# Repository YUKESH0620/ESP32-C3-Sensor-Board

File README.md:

# ESP32-C3 Smart Sensor Board

This repository contains the complete **hardware design** of a custom **ESP32-C3 based Smart Sensor Board**, including schematics, PCB layout, and documentation.

The design integrates **robust power management, multiple sensors, data storage, USB connectivity, and auto-programming**, making it suitable for **IoT, data logging, and embedded systems development**.

---

##  Board Images

###  Complete Schematic

###  PCB Layout

###  3D Views

---

##  System Architecture

### Functional Block Diagram
```text
USB-C / Li-Po Battery
│
MCP73831 Charger
│
+5V Rail
│
LM1117-3.3 LDO
│
+3.3V Rail
│
ESP32-C3 MCU
│ │ │ │
│ │ │ Microphone + MAX4466
│ │ BME280 (I2C)
│ LDR (ADC)
SD Card (SPI)
|
SPI Flash
```
---

##  Key Features

###  Power & Charging
- USB Type-C connector
- Li-Po charging using **MCP73831**
- JST battery connector
- LM1117-3.3 LDO regulator
- Power status LED

###  Microcontroller
- **ESP32-C3-WROOM-02**
- RISC-V core
- Wi-Fi + BLE
- USB-UART programmable

###  Sensors
- **BME280** – Temperature, humidity, pressure
- **Electret microphone + MAX4466 amplifier**
- **LDR photo sensor**

###  Storage
- SPI Flash memory (W25Q32)
- Micro SD card module (SPI)

###  Programming & Debug
- CP2102N USB-to-UART
- Auto-programming (DTR/RTS → EN/BOOT)
- Boot & Reset buttons
- Test points

---

##  Working Principle

### Power Section
- USB-C provides 5V
- MCP73831 safely charges Li-Po battery
- LM1117 converts 5V to regulated 3.3V
- Decoupling capacitors ensure stable rails

### MCU & Sensors
- ESP32-C3 communicates with:
  - BME280 via I²C
  - SD card & Flash via SPI
  - Microphone and LDR via ADC
- Data can be logged or transmitted wirelessly

### Programming
- USB-C → CP2102N
- DTR/RTS control BOOT & EN automatically
- Compatible with ESP-IDF and Arduino

---

## 🧾 Bill of Materials

###  Active Components

| Ref | Component | Value / Part |
|----|----------|-------------|
| U1 | ESP32 MCU | ESP32-C3-WROOM-02 |
| U2 | Env Sensor | BME280 |
| U3 | USB-UART | CP2102N |
| U4 | Charger IC | MCP73831 |
| U5 | LDO Regulator | LM1117-3.3 |
| U6 | SPI Flash | W25Q32 |
| U7 | Mic Amplifier | MAX4466 |
| J1 | USB Connector | USB Type-C |
| J2 | Battery Connector | JST-PH-2 |
| J3 | SD Card Socket | SPI SD |

---

###  Resistors (From Schematic)

| Ref | Value | Purpose |
|----|------|--------|
| R1 | 10kΩ | MCP73831 PROG |
| R2 | 10kΩ | MCP73831 PROG |
| R3 | 5.1kΩ | USB-C CC pull-down |
| R4 | 5.1kΩ | USB-C CC pull-down |
| R5 | 2kΩ | MCP73831 status |
| R6 | 20kΩ | MCP73831 status |
| R7 | 470Ω | Charging LED |
| R8 | 470Ω | Charged LED |
| R9 | 470Ω | Fault LED |
| R10 | 470Ω | Power LED |
| R11 | 1kΩ | USB VBUS link |
| R12 | 22.1kΩ | USB detection |
| R13 | 47.5kΩ | USB detection |
| R15 | 47k | Biasing resistor |
| R23 | 10kΩ | LDR voltage divider |
| R24 | 4.7kΩ | I²C pull-up |
| R25 | 4.7kΩ | I²C pull-up |
| R26 | 2kΩ | Mic bias |
| R27 | 1MΩ | Mic amp gain |
| R28 | 2kΩ | Mic bias |
| R29 | 1MΩ | Mic amp gain |
| R30 | 10kΩ | Mic amp |
| R31 | 2.2kΩ | Mic feedback |
| R32 | 10kΩ | Reset pull-up |
| R33 | 10kΩ | DTR control |
| R34 | 10kΩ | RTS control |

---

###  Capacitors (From Schematic)

| Ref | Value | Purpose |
|----|------|--------|
| C1 | 0.1µF | USB decoupling |
| C2 | 0.1µF | LDO input |
| C3 | 10µF | LDO bulk |
| C4 | 10µF | LDO output |
| C5 | 0.1µF | LDO output |
| C6 | 1µF | MCP73831 |
| C7 | 10µF | ESP32 supply |
| C8 | 0.1µF | ESP32 decoupling |
| C10 | 0.1µF | Sensor decoupling |
| C14 | 0.1µF | Flash decoupling |
| C15 | 0.1µF | BME280 |
| C17 | 10nF | Mic coupling |
| C18 | 0.1µF | Mic supply |
| C19 | 1µF | Mic amp |
| C20 | 0.1µF | Mic feedback |
| C21 | 0.1µF | BOOT debounce |
| C22 | 1µF | RESET debounce |

---

##  Design Considerations

- Ground plane for EMI reduction
- ESP32 antenna keep-out respected
- Separate analog routing for microphone
- Decoupling capacitors close to ICs
- USB-C CC resistors correctly implemented
- Battery charging current set safely

---

##  Testing Strategy

- Power rail validation
- USB enumeration
- Battery charge & termination test
- Sensor I²C/SPI verification
- SD card read/write
- ADC noise testing (mic & LDR)

---
##  Revision History

### Rev-A (Initial Prototype)
- ESP32-C3 based sensor board
- Microphone connected to GPIO5 (ADC conflict with Wi-Fi)
- Fixed-gain microphone amplifier
- Photosensor output taken from incorrect pin
- No additional EMI filtering on power path

### Rev-B (Improved Design – Current)
- Resolved ADC conflict between Wi-Fi and microphone
- Improved analog signal quality
- Added EMI noise suppression
- Improved user interface and usability
---

##  Key Engineering Fixes & Improvements

### 1. ADC Conflict Resolution (Wi-Fi vs Microphone)
- Issue identified during testing: GPIO5 ADC unavailable when Wi-Fi is active
- Root cause: ADC resource conflict on ESP32-C3
- Solution:
  - Microphone OUT moved from GPIO5 → GPIO0 (ADC1)
  - CS_SD reassigned to GPIO5 as digital output
- Result: Microphone and Wi-Fi now operate simultaneously without conflict

### 2. Variable Gain Microphone Amplifier
- Replaced fixed gain network with trimmer potentiometer
- Gain range adjustable from **25× to 125×**
- Improves adaptability for different acoustic environments

### 3. Photosensor Signal Correction
- Output pin corrected from pin 3 → pin 1 as per datasheet
- Added RC filtering capacitors for noise reduction
- Result: Stable and accurate ADC readings

### 4. Analog Noise Reduction
- Added local decoupling capacitor near GPIO0 (MIC_OUT)
- Reduced high-frequency noise on ADC line

### 5. Improved User Interface
- Replaced small tact switches with larger buttons
- Better usability and reliability

### 6. Power Integrity Enhancement
- Added ferrite bead on charger output
- Purpose:
  - Suppress high-frequency switching noise from MCP73871
  - Reduce EMI affecting analog and RF sections

---
##  Design Status

- Rev-A: Initial schematic completed and reviewed
- Design improvements identified during schematic review
- Rev-B incorporates recommended fixes and optimizations
- Hardware fabrication and testing are pending

Note: Functional validation will be performed after PCB fabrication.

---
##  Validation Plan (Post-Fabrication)

- Verify Wi-Fi and microphone operation simultaneously
- Validate ADC stability for photosensor input
- Measure microphone gain range
- Check power rail noise and EMI behavior
- Confirm battery charging and boost operation

---

##  Applications

- Environmental monitoring
- IoT data logger
- Smart sensor node
- Academic & portfolio project
- Embedded systems experimentation

---

##  Future Enhancements

- Fuel gauge IC
- Enclosure design
- OTA firmware support
- EMI compliance testing
- Low-power optimization

---

## 👤 Author

**Yukesh S**  
Embedded Systems Enthusiast  

---

## 📜 License

This project is licensed under the MIT License.

You are free to use, modify, distribute, and commercialize this design,
provided that the original copyright notice and license text are included.

See the [LICENSE](LICENSE) file for full details.

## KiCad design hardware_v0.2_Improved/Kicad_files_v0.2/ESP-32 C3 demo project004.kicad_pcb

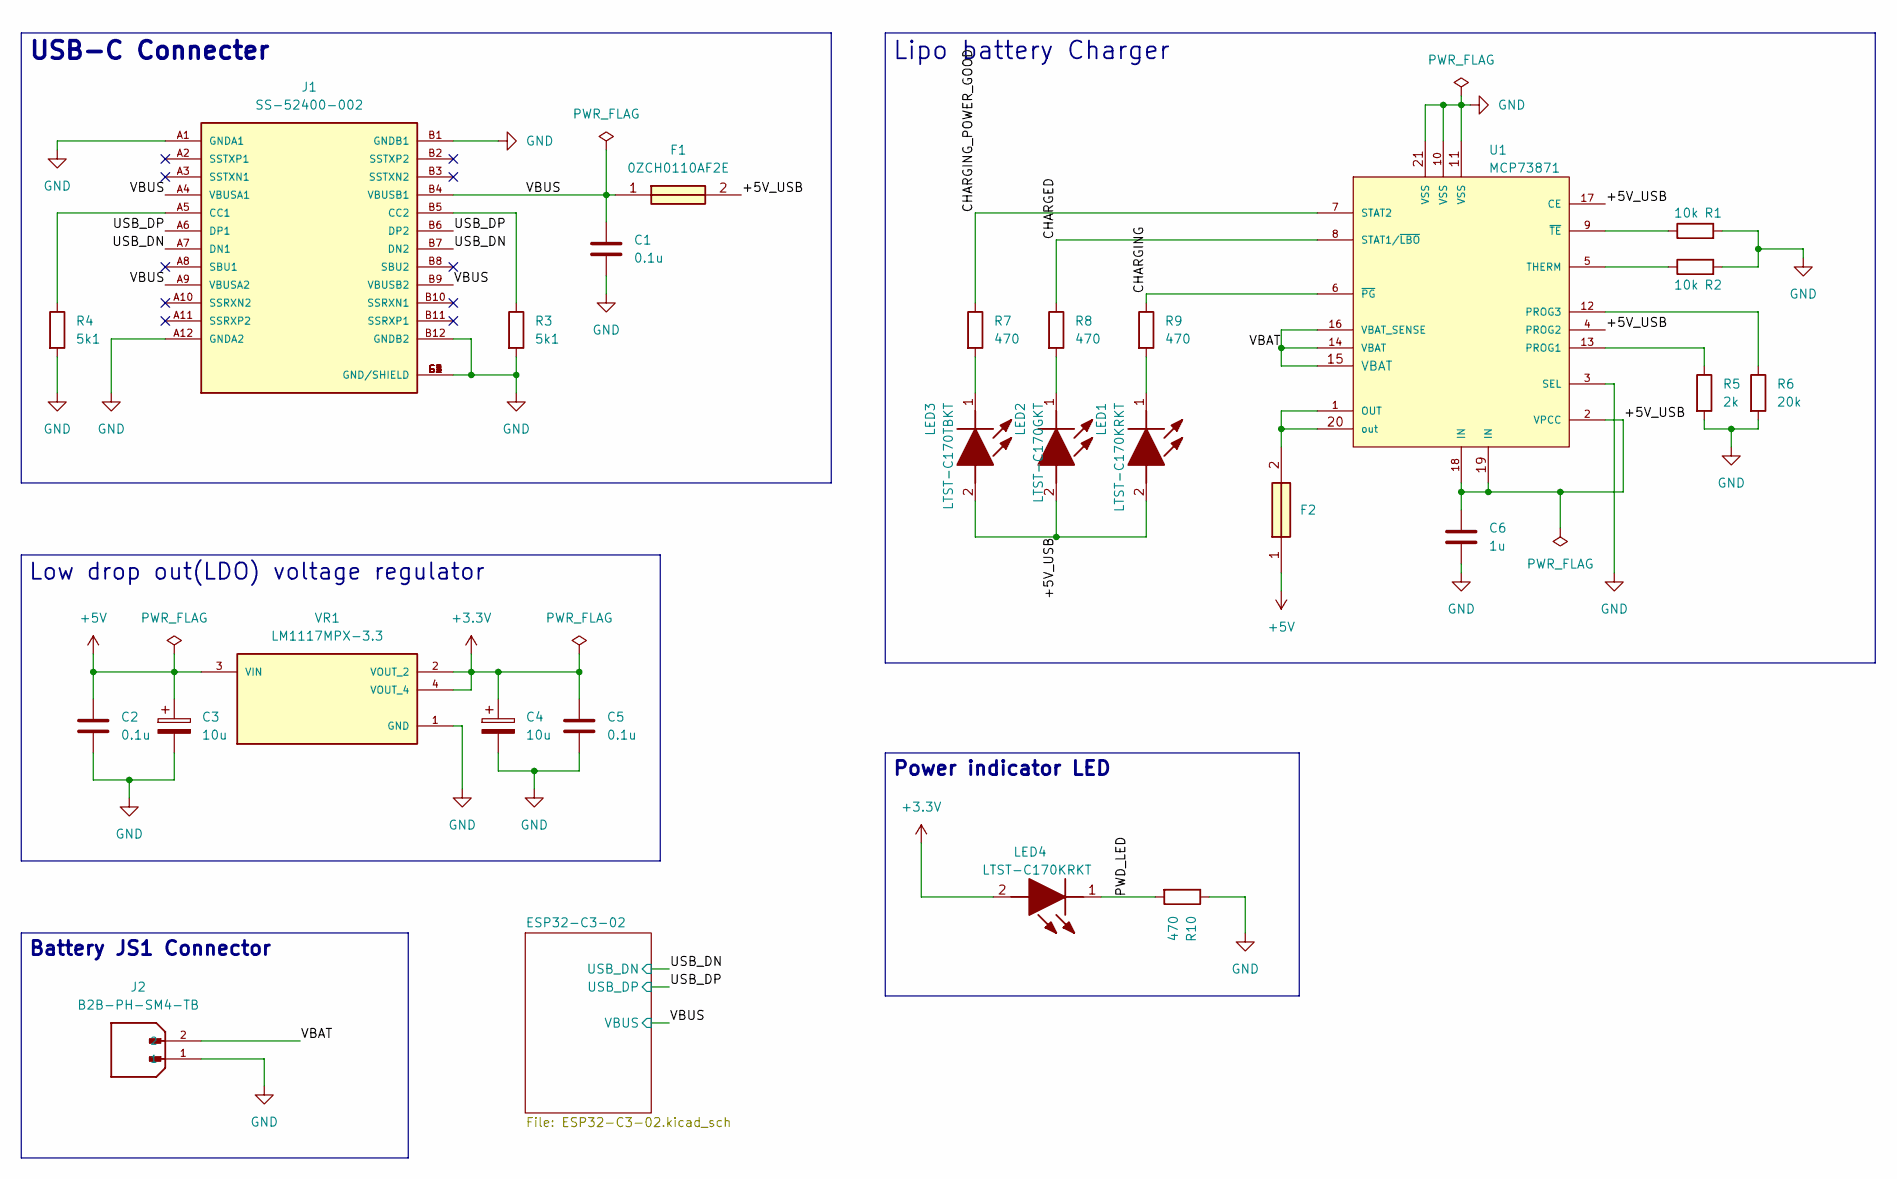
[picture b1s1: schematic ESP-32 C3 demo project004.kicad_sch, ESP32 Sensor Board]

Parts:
C1, C2, C5: 0.1u; C_0805_2012Metric
C3, C4: 10u; T491A
C6: 1u; C_0805_2012Metric
F1, F2: 0ZCH0110AF2E; FUSC3226X100N; Manufacturer_Part_Number 0ZCH0110AF2E
J1: SS-52400-002; BELFUSE_SS-52400-002; PARTREV A0
J2: B2B-PH-SM4-TB; JST_B2B-PH-SM4-TB; PARTREV N/A
LED1, LED4: LTST-C170KRKT; LEDC2012X120N; Manufacturer_Part_Number LTST-C170KRKT; Mouser Part Number 859-LTST-C170KRKT
LED2: LTST-C170GKT; LEDC2012X120N; Manufacturer_Part_Number LTST-C170GKT; Mouser Part Number 859-LTST-C170GKT
LED3: LTST-C170TBKT; LEDC2012X120N; Manufacturer_Part_Number LTST-C170TBKT; Mouser Part Number 859-LTST-C170TBKT
R1, R2: 10k; R_0805_2012Metric
R3, R4: 5k1; R_0805_2012Metric
R5: 2k; R_0805_2012Metric
R6: 20k; R_0805_2012Metric
R7, R8, R9, R10: 470; R_0805_2012Metric
U1: MCP73871; QFN50P400X400X100-21N; PARTREV D
VR1: LM1117MPX-3.3; VREG_LM1117MPX-3.3

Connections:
+3.3V: C4.1, C5.1, LED4.2 (A), VR1.2 (VOUT_2), VR1.4 (VOUT_4); also elsewhere on the board
+5V: C2.1, C3.1, F2.1, VR1.3 (VIN)
/+5V_USB: C6.1, F1.2, LED1.2 (A), LED2.2 (A), LED3.2 (A), U1.2 (VPCC), U1.4 (PROG2), U1.17 (CE), U1.18 (IN), U1.19 (IN)
/CHARGED: R8.1, U1.8 (STAT1/~LBO)
/CHARGING: R9.1, U1.6 (~PG)
/CHARGING_POWER_GOOD: R7.1, U1.7 (STAT2)
/PWD_LED: LED4.1 (K), R10.2
/USB_DN: J1.A7 (DN1), J1.B7 (DN2); also elsewhere on the board
/USB_DP: J1.A6 (DP1), J1.B6 (DP2); also elsewhere on the board
/VBAT: J2.2, U1.14 (VBAT), U1.15 (VBAT), U1.16 (VBAT_SENSE)
/VBUS: C1.1, F1.1, J1.A4 (VBUSA1), J1.A9 (VBUSA2), J1.B4 (VBUSB1), J1.B9 (VBUSB2); also elsewhere on the board
GND: C1.2, C2.2, C3.2, C4.2, C5.2, C6.2, J1.A1 (GNDA1), J1.A12 (GNDA2), J1.B1 (GNDB1), J1.B12 (GNDB2), J1.G1 (GND/SHIELD), J1.G2 (GND/SHIELD), J1.G3 (GND/SHIELD), J1.G4 (GND/SHIELD), J1.S1 (GND/SHIELD), J1.S2 (GND/SHIELD), J1.S3 (GND/SHIELD), J1.S4 (GND/SHIELD), J2.1, R1.2, R2.2, R3.2, R4.2, R5.2, R6.2, R10.1, U1.3 (SEL), U1.10 (VSS), U1.11 (VSS), U1.21 (VSS), VR1.1 (GND); also elsewhere on the board
unnamed: J1.A5 (CC1), R4.1
unnamed: J1.B5 (CC2), R3.1
unnamed: LED1.1 (K), R9.2
unnamed: LED2.1 (K), R8.2
unnamed: LED3.1 (K), R7.2
unnamed: F2.2, U1.1 (OUT), U1.20 (out)
unnamed: R5.1, U1.13 (PROG1)
unnamed: R6.1, U1.12 (PROG3)
unnamed: R2.1, U1.5 (THERM)
unnamed: R1.1, U1.9 (~TE)

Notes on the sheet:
Lipo battery Charger
USB-C Connecter
Power indicator LED
Battery JS1 Connector
Low drop out(LDO) voltage regulator

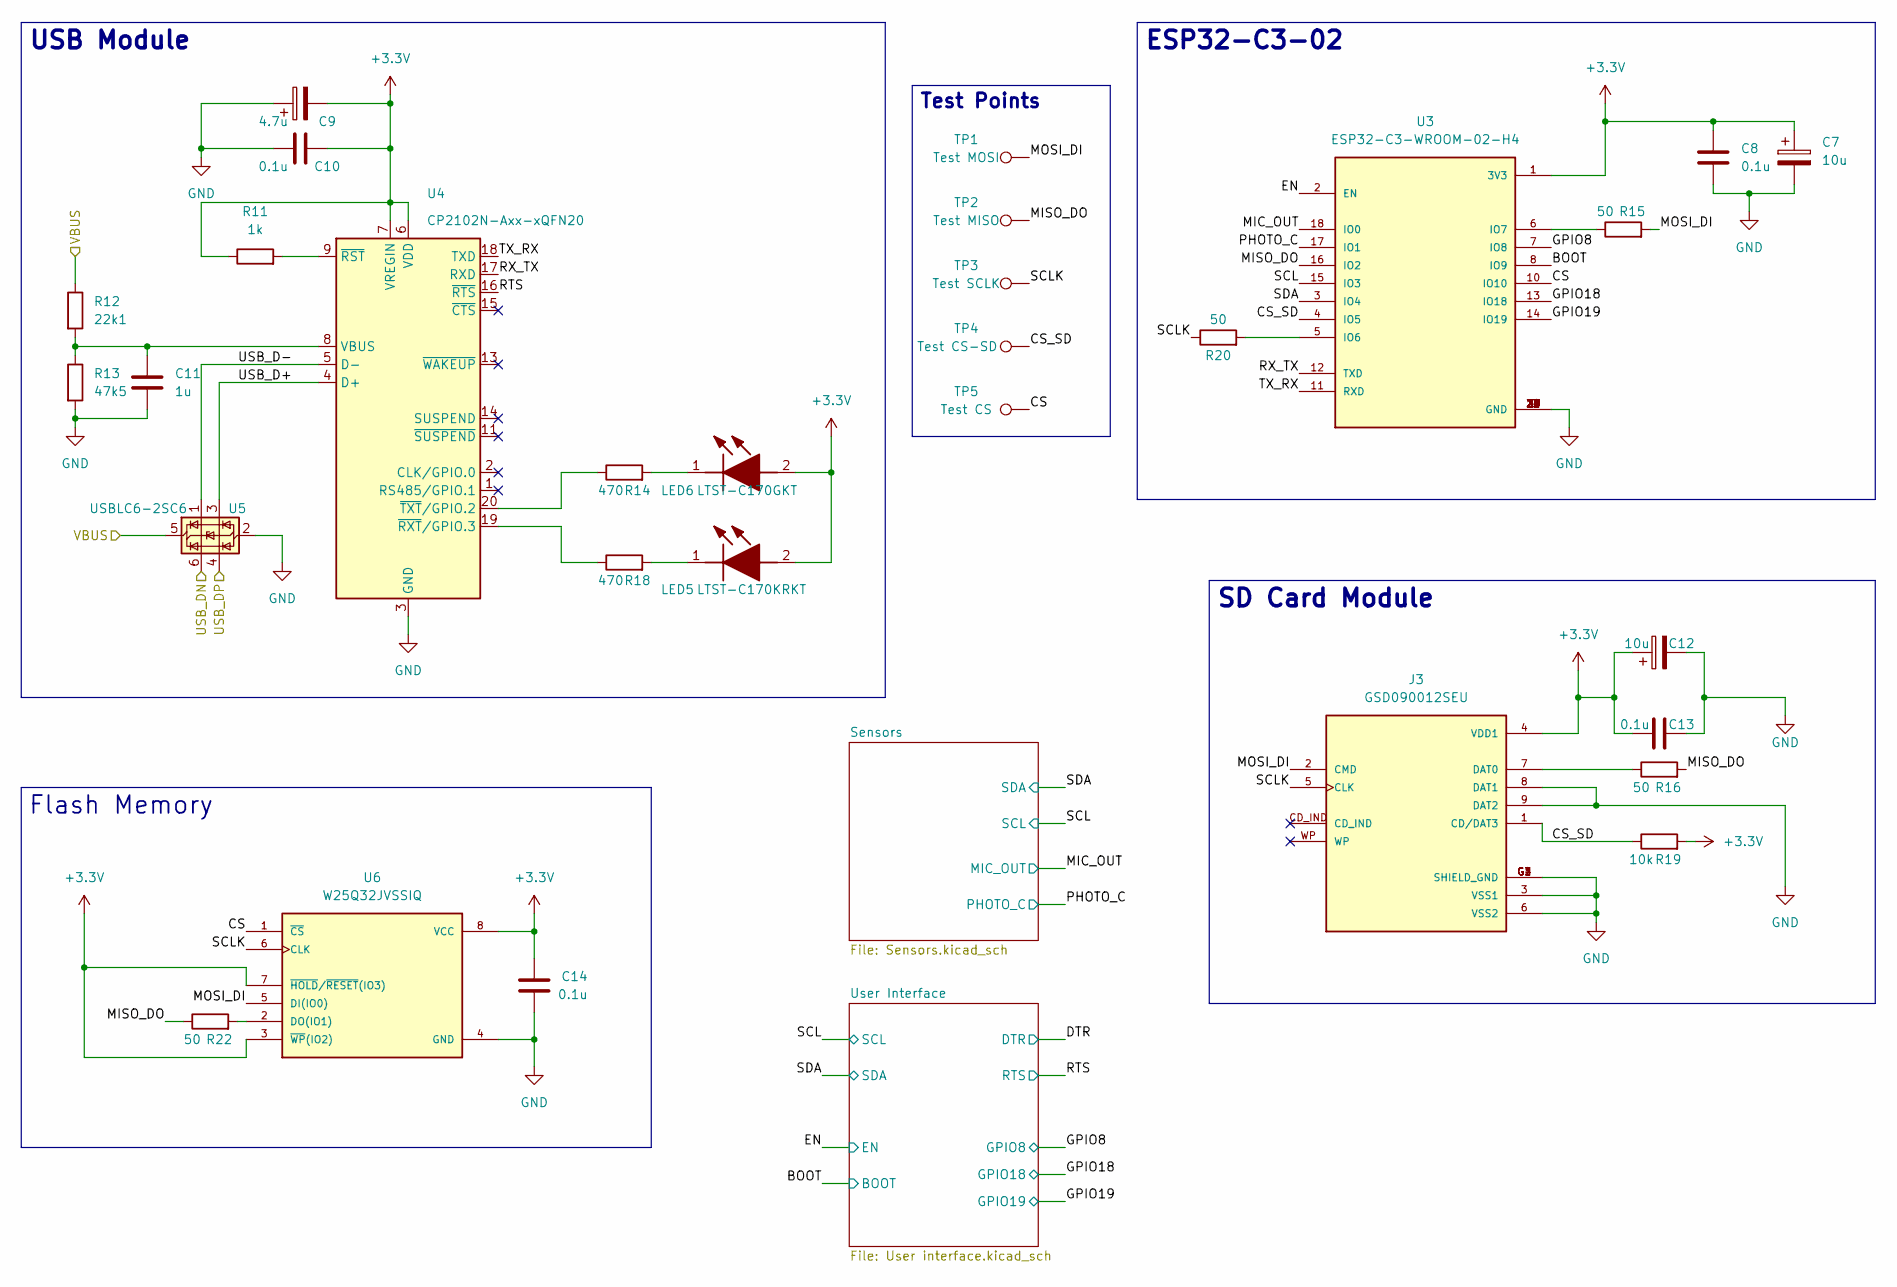
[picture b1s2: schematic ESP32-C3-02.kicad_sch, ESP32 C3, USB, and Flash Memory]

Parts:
C7, C12: 10u; T491A
C8, C10, C13, C14: 0.1u; C_0805_2012Metric
C9: 4.7u; T491A
C11: 1u; C_0805_2012Metric
J3: GSD090012SEU; AMPHENOL_GSD090012SEU; PARTREV E
LED5: LTST-C170GKT; LEDC2012X120N; Manufacturer_Part_Number LTST-C170GKT; Mouser Part Number 859-LTST-C170GKT
LED6: LTST-C170KRKT; LEDC2012X120N; Manufacturer_Part_Number LTST-C170KRKT; Mouser Part Number 859-LTST-C170KRKT
R11: 1k; R_0805_2012Metric
R12: 22k1; R_0805_2012Metric
R13: 47k5; R_0805_2012Metric
R14, R18: 470; R_0805_2012Metric
R15, R16, R20, R22: 50; R_0805_2012Metric
R19: 10k; R_0805_2012Metric
TP1: Test MOSI; TestPoint_Pad_D1.0mm
TP2: Test MISO; TestPoint_Pad_D1.0mm
TP3: Test SCLK; TestPoint_Pad_D1.0mm
TP4: Test CS-SD; TestPoint_Pad_D1.0mm
TP5: Test CS; TestPoint_Pad_D1.0mm
U3: ESP32-C3-WROOM-02-H4; MODULE_ESP32-C3-WROOM-02-H4
U4: CP2102N-Axx-xQFN20; QFN50P400X400X100-21N
U5: USBLC6-2SC6; SOT-23-6
U6: W25Q32JVSSIQ; SOIC127P790X216-8N; M_PART_NUMBER W25QXX

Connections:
+3.3V: C7.1, C8.1, C9.2, C10.2, C12.1, C13.1, C14.2, J3.4 (VDD1), LED5.2 (A), LED6.2 (A), R11.1, R19.2, U3.1 (3V3), U4.6 (VDD), U4.7 (VREGIN), U6.3 (~WP(IO2)), U6.7 (~HOLD/~RESET(IO3)), U6.8 (VCC); also elsewhere on the board
/ESP32-C3-02/BOOT: U3.8 (IO9); also elsewhere on the board
/ESP32-C3-02/CS: TP5.1, U3.10 (IO10), U6.1 (~CS)
/ESP32-C3-02/CS_SD: J3.1 (CD/DAT3), R19.1, TP4.1, U3.4 (IO5)
/ESP32-C3-02/EN: U3.2 (EN); also elsewhere on the board
/ESP32-C3-02/GPIO8: U3.7 (IO8); also elsewhere on the board
/ESP32-C3-02/GPIO18: U3.13 (IO18); also elsewhere on the board
/ESP32-C3-02/GPIO19: U3.14 (IO19); also elsewhere on the board
/ESP32-C3-02/MIC_OUT: U3.18 (IO0); also elsewhere on the board
/ESP32-C3-02/MISO_DO: R16.2, R22.1, TP2.1, U3.16 (IO2)
/ESP32-C3-02/MOSI_DI: J3.2 (CMD), R15.2, TP1.1, U6.5 (DI(IO0))
/ESP32-C3-02/PHOTO_C: U3.17 (IO1); also elsewhere on the board
/ESP32-C3-02/RTS: U4.16 (~RTS); also elsewhere on the board
/ESP32-C3-02/RX_TX: U3.12 (TXD), U4.17 (RXD)
/ESP32-C3-02/SCL: U3.15 (IO3); also elsewhere on the board
/ESP32-C3-02/SCLK: J3.5 (CLK), R20.1, TP3.1, U6.6 (CLK)
/ESP32-C3-02/SDA: U3.3 (IO4); also elsewhere on the board
/ESP32-C3-02/TX_RX: U3.11 (RXD), U4.18 (TXD)
/ESP32-C3-02/USB_D+: U4.4 (D+), U5.3 (I/O2)
/ESP32-C3-02/USB_D-: U4.5 (D-), U5.1 (I/O1)
/USB_DN: U5.6 (I/O1); also elsewhere on the board
/USB_DP: U5.4 (I/O2); also elsewhere on the board
/VBUS: R12.1, U5.5 (VBUS); also elsewhere on the board
GND: C7.2, C8.2, C9.1, C10.1, C11.2, C12.2, C13.2, C14.1, J3.3 (VSS1), J3.6 (VSS2), J3.8 (DAT1), J3.9 (DAT2), J3.G1 (SHIELD_GND), J3.G2 (SHIELD_GND), J3.G3 (SHIELD_GND), J3.G4 (SHIELD_GND), R13.2, U3.9 (GND), U3.19 (GND), U3.20 (GND), U3.21 (GND), U3.22 (GND), U3.23 (GND), U3.24 (GND), U3.25 (GND), U3.26 (GND), U3.27 (GND), U3.28 (GND), U3.29 (GND), U3.30 (GND), U3.31 (GND), U3.32 (GND), U3.33 (GND), U3.34 (GND), U3.35 (GND), U3.36 (GND), U3.37 (GND), U3.38 (GND), U3.39 (GND), U4.3 (GND), U4.12 (GND), U4.21 (GND), U5.2 (GND), U6.4 (GND); also elsewhere on the board
unnamed: J3.7 (DAT0), R16.1
unnamed: LED5.1 (K), R14.2
unnamed: LED6.1 (K), R18.2
unnamed: R20.2, U3.5 (IO6)
unnamed: R15.1, U3.6 (IO7)
unnamed: C11.1, R12.2, R13.1, U4.8 (VBUS)
unnamed: R11.2, U4.9 (~RST)
unnamed: R18.1, U4.19 (~RXT/GPIO.3)
unnamed: R14.1, U4.20 (~TXT/GPIO.2)
unnamed: R22.2, U6.2 (DO(IO1))

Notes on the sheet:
SD Card Module
Flash Memory
ESP32-C3-02
Test Points
USB Module

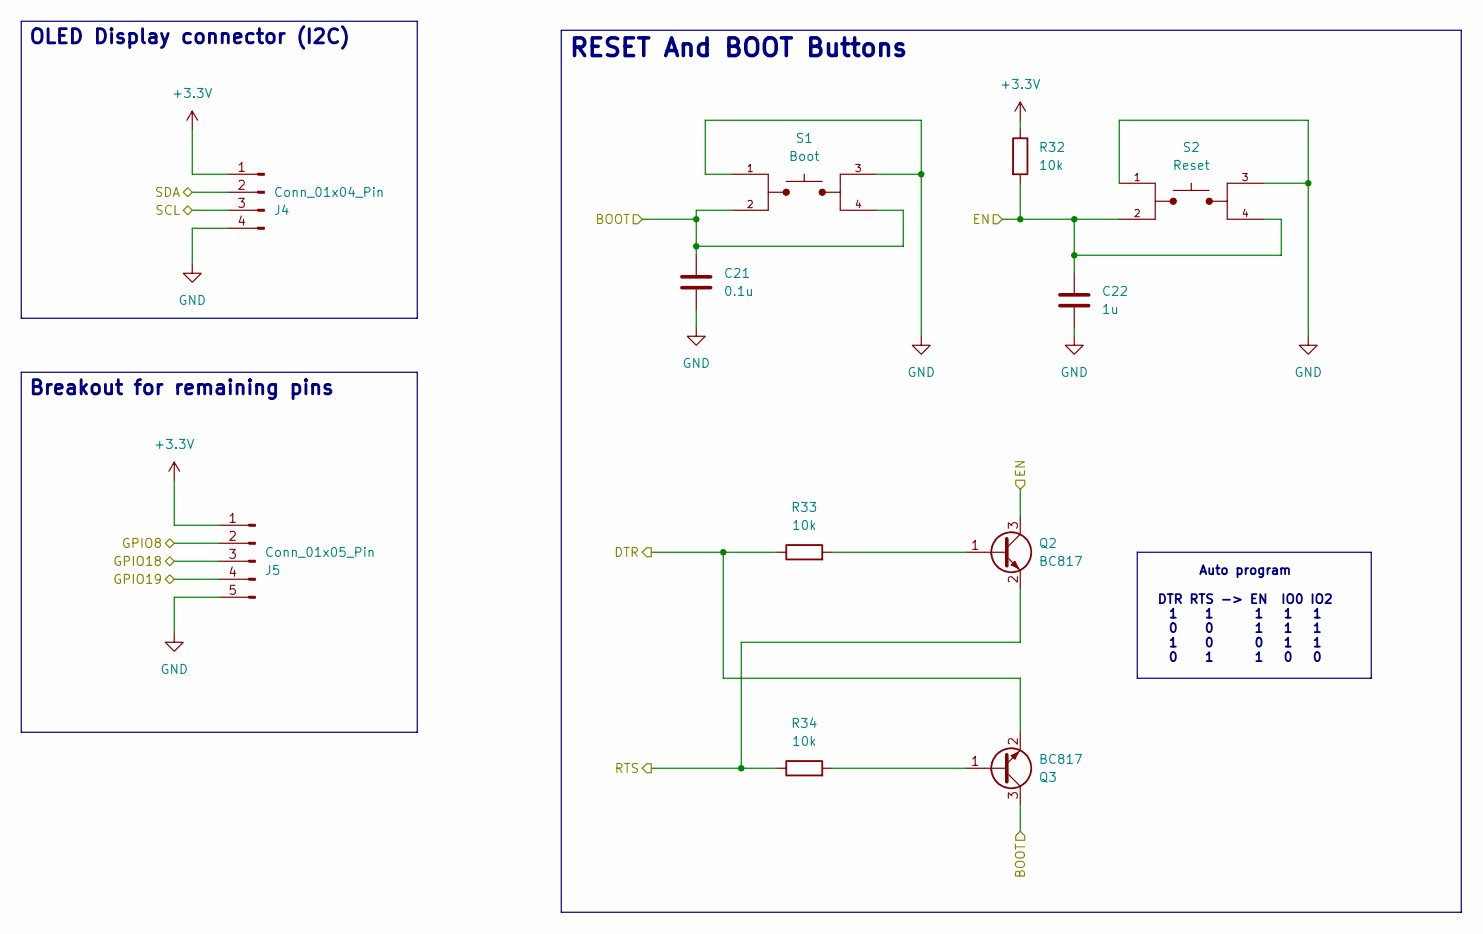
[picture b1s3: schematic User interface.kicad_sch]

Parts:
C21: 0.1u; C_0805_2012Metric
C22: 1u; C_0805_2012Metric
J4: Conn_01x04_Pin; PinHeader_1x04_P2.54mm_Vertical
J5: Conn_01x05_Pin; PinHeader_1x05_P2.54mm_Vertical
Q2, Q3: BC817; SOT-23
R32, R33, R34: 10k; R_0805_2012Metric
S1: Boot; SW_TL3305AF260QG; PARTREV C
S2: Reset; SW_TL3305AF260QG; PARTREV C

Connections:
+3.3V: J4.1, J5.1, R32.1; also elsewhere on the board
/ESP32-C3-02/BOOT: C21.1, Q3.3 (C), S1.2, S1.4; also elsewhere on the board
/ESP32-C3-02/DTR: Q3.2 (E), R33.1
/ESP32-C3-02/EN: C22.1, Q2.3 (C), R32.2, S2.2, S2.4; also elsewhere on the board
/ESP32-C3-02/GPIO8: J5.2; also elsewhere on the board
/ESP32-C3-02/GPIO18: J5.3; also elsewhere on the board
/ESP32-C3-02/GPIO19: J5.4; also elsewhere on the board
/ESP32-C3-02/RTS: Q2.2 (E), R34.1; also elsewhere on the board
/ESP32-C3-02/SCL: J4.3; also elsewhere on the board
/ESP32-C3-02/SDA: J4.2; also elsewhere on the board
GND: C21.2, C22.2, J4.4, J5.5, S1.1, S1.3, S2.1, S2.3; also elsewhere on the board
unnamed: Q2.1 (B), R33.2
unnamed: Q3.1 (B), R34.2

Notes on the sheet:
Auto program DTR RTS -> EN IO0 IO2 1 1 1 1 1 0 0 1 1 1 1 0 0 1 1 0 1 1 0 0
Breakout for remaining pins
RESET And BOOT Buttons
OLED Display connector (I2C)

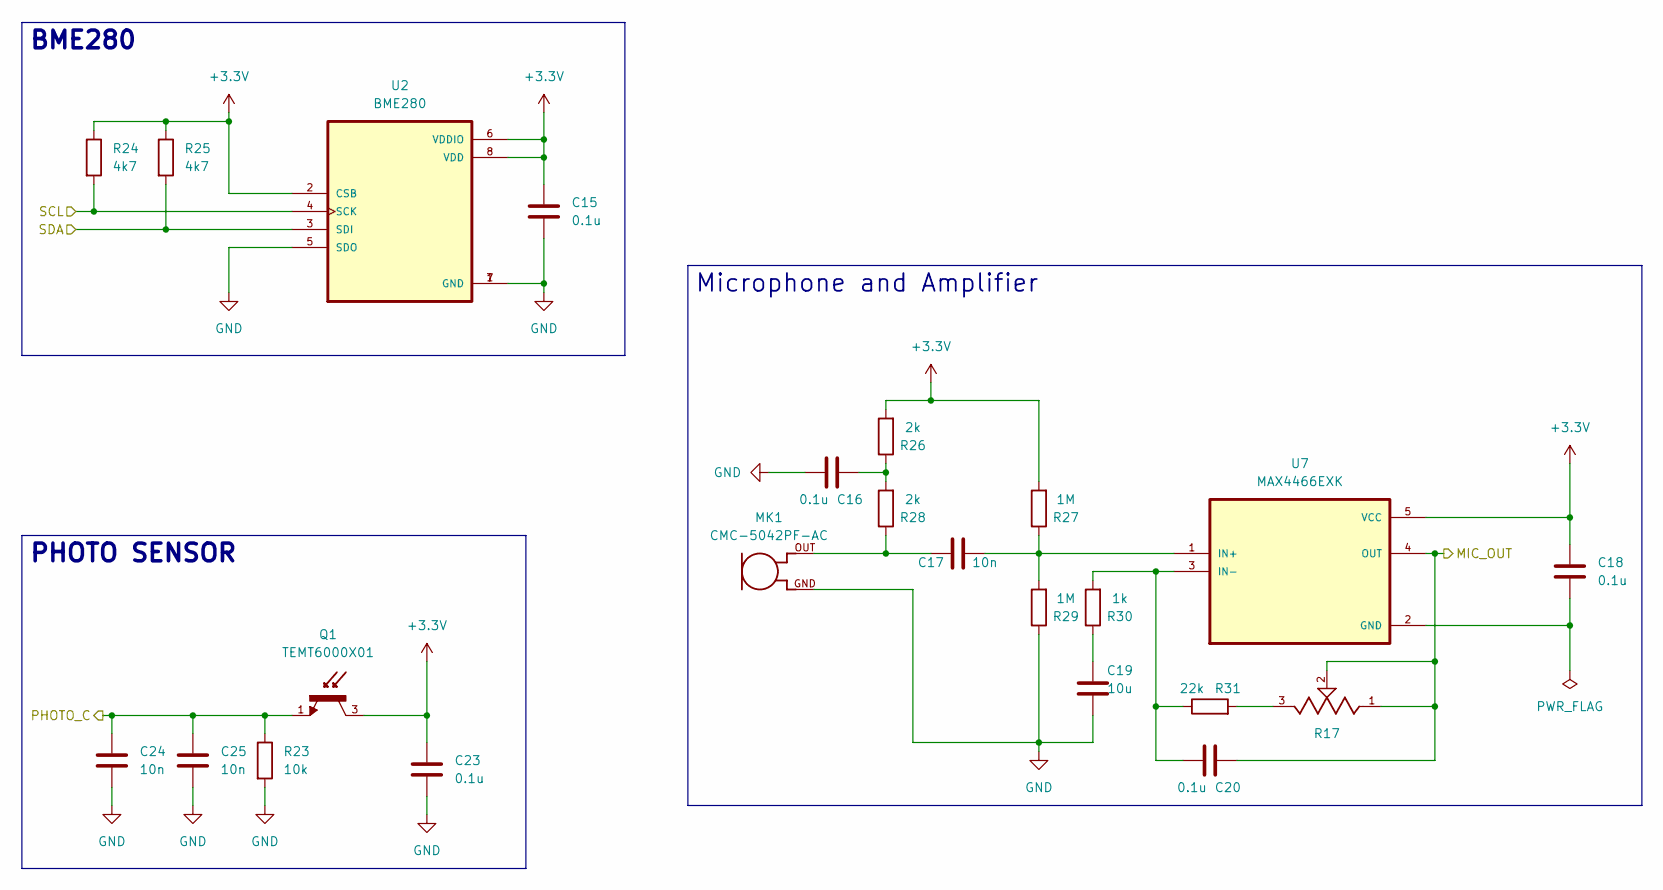
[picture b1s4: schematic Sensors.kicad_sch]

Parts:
C15, C16, C18, C20, C23: 0.1u; C_0805_2012Metric
C17, C24, C25: 10n; C_0805_2012Metric
C19: 10u; C_0805_2012Metric
MK1: CMC-5042PF-AC; CUI_CMC-5042PF-AC
Q1: TEMT6000X01; TRANS_TEMT6000X01; PARTREV 1.9
R17: 35WR100KLFTR; TRIM_35WR100KLFTR; PARTREV D
R23: 10k; R_0805_2012Metric
R24, R25: 4k7; R_0805_2012Metric
R26, R28: 2k; R_0805_2012Metric
R27, R29: 1M; R_0805_2012Metric
R30: 1k; R_0805_2012Metric
R31: 22k; R_0805_2012Metric
U2: BME280; PSON65P250X250X100-8N
U7: MAX4466EXK; SOT65P210X110-5N

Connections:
+3.3V: C15.1, C18.1, C23.1, Q1.3, R24.1, R25.1, R26.2, R27.2, U2.2 (CSB), U2.6 (VDDIO), U2.8 (VDD), U7.5 (VCC); also elsewhere on the board
/ESP32-C3-02/MIC_OUT: C20.2, R17.1, R17.2, U7.4 (OUT); also elsewhere on the board
/ESP32-C3-02/PHOTO_C: C24.1, C25.1, Q1.1, R23.1; also elsewhere on the board
/ESP32-C3-02/SCL: R24.2, U2.4 (SCK); also elsewhere on the board
/ESP32-C3-02/SDA: R25.2, U2.3 (SDI); also elsewhere on the board
GND: C15.2, C16.1, C19.1, C23.2, C24.2, C25.2, MK1.GND, R23.2, R29.1, U2.1 (GND), U2.5 (SDO), U2.7 (GND); also elsewhere on the board
unnamed: C16.2, R26.1, R28.2
unnamed: C17.2, MK1.OUT, R28.1
unnamed: C19.2, R30.1
unnamed: R17.3, R31.2
unnamed: C18.2, U7.2 (GND)
unnamed: C17.1, R27.1, R29.2, U7.1 (IN+)
unnamed: C20.1, R30.2, R31.1, U7.3 (IN-)

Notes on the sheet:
BME280
Microphone and Amplifier
PHOTO SENSOR

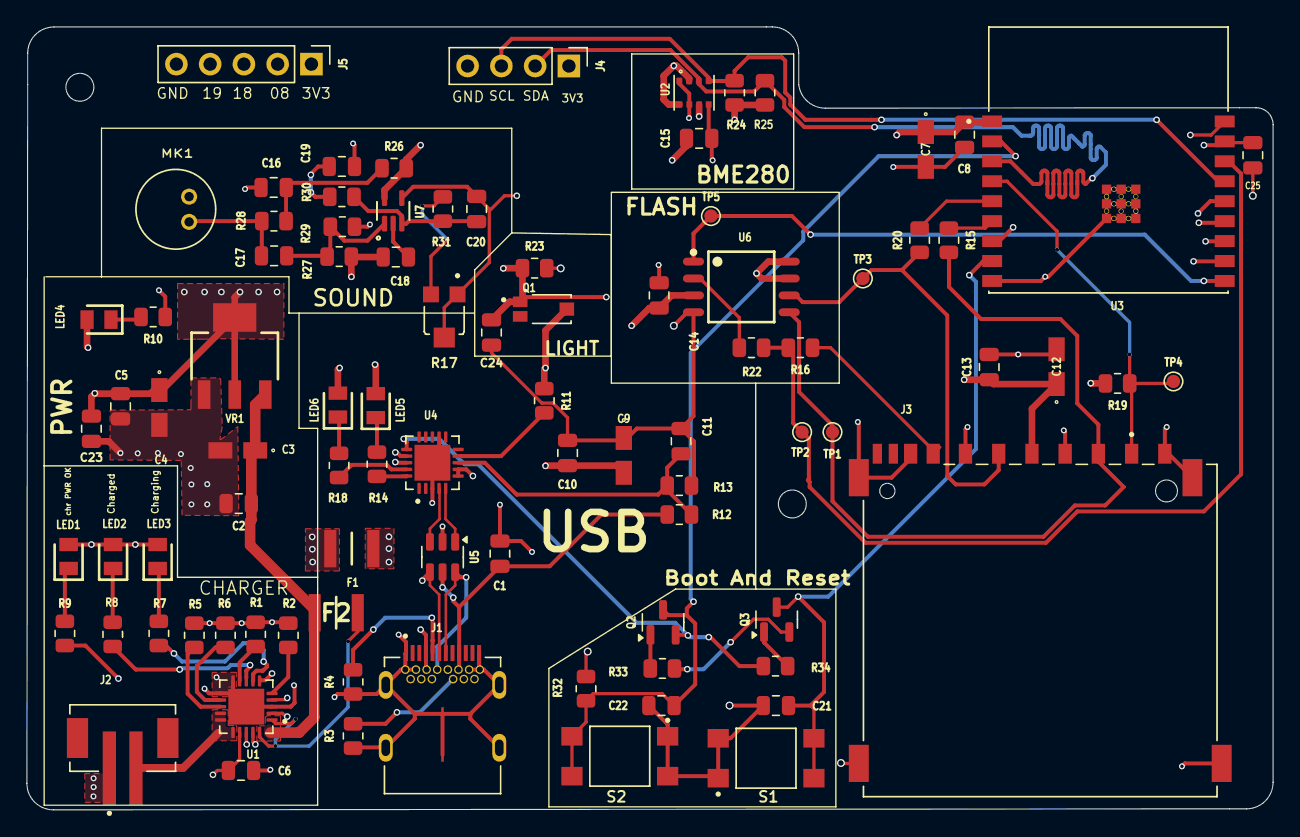
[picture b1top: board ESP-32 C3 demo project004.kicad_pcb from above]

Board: 4 copper layers, 93.8 x 58.9 mm, 90 parts (0 on the bottom side), 61 nets.

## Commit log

2025-12-26 Create 3D_View
2025-12-30 Rename .gitkeep to .gitkeep
